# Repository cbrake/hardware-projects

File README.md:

# Hardware Projects

Various hardware projects and notes.

Simple IoT hardware designs have moved to:
https://github.com/simpleiot/hardware

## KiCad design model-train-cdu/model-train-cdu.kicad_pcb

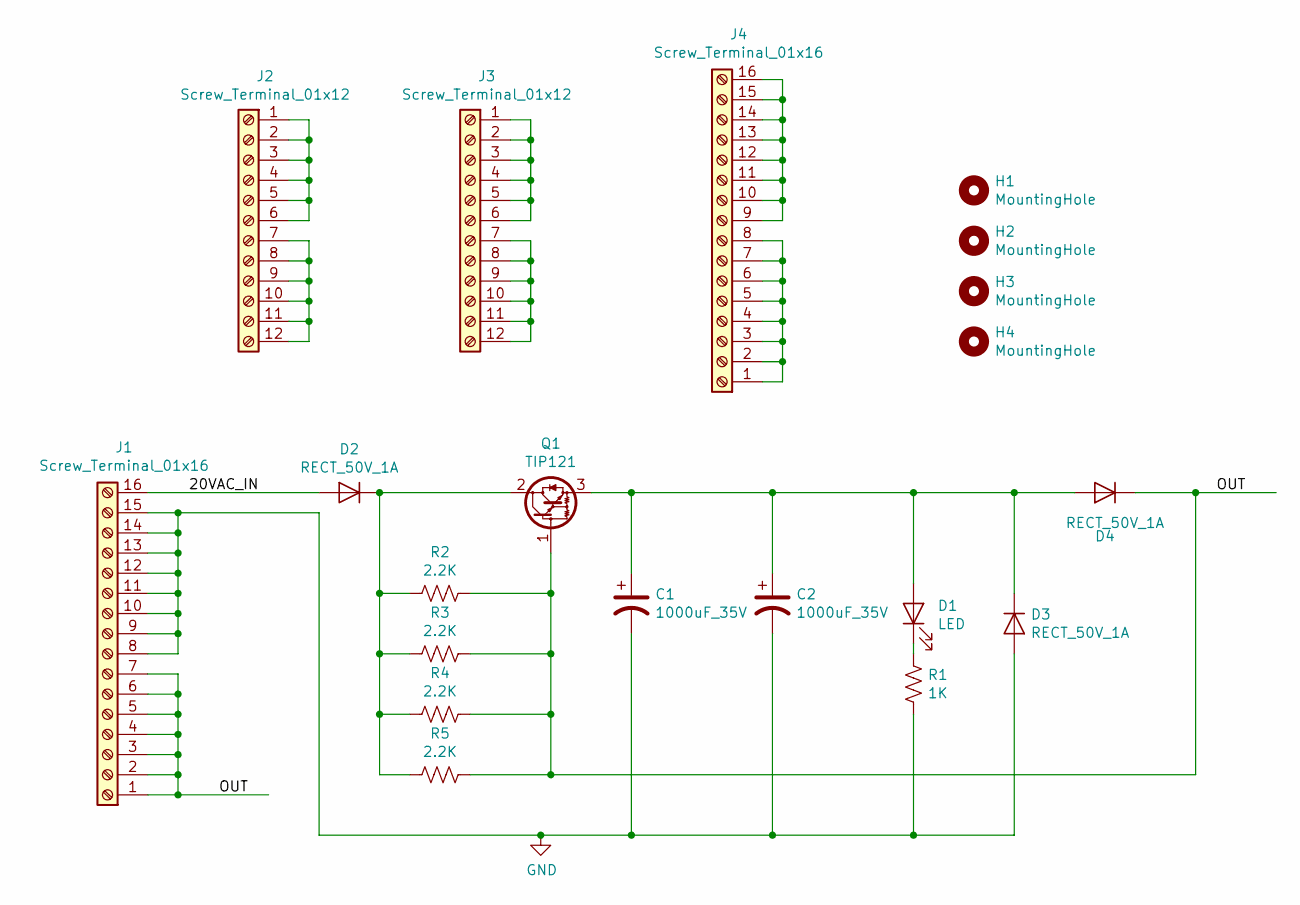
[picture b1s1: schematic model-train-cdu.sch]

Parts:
C1, C2: 1000uF_35V; CP_Radial_D10.0mm_P5.00mm; MPN EEU-FS1V102LB
D1: LED; LED_3mm_Radial
D2, D3, D4: RECT_50V_1A; D_SMA; MPN US1M-13-F
H1, H2, H3, H4: MountingHole; MountingHole_4.3mm_M4
J1, J4: Screw_Terminal_01x16; TerminalBlock_Phoenix_PT-1,5-16-5.0-H_1x16_P5.00mm_Horizont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
J2, J3: Screw_Terminal_01x12; TerminalBlock_Phoenix_PT-1,5-12-5.0-H_1x12_P5.00mm_Horizont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
Q1: TIP121; TO-220-3_Horizontal_TabDown
R1: 1K; R_1206_3216Metric
R2, R3, R4, R5: 2.2K; R_1206_3216Metric

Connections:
/20VAC_IN: D2.2 (A), J1.16
/OUT: D4.1 (K), J1.1, J1.2, J1.3, J1.4, J1.5, J1.6, J1.7, Q1.1 (B), R2.1, R3.1, R4.1, R5.1
GND: C1.2, C2.2, D3.2 (A), J1.8, J1.9, J1.10, J1.11, J1.12, J1.13, J1.14, J1.15, R1.2
unnamed: C1.1, C2.1, D1.2 (A), D3.1 (K), D4.2 (A), Q1.3 (E)
unnamed: D1.1 (K), R1.1
unnamed: D2.1 (K), Q1.2 (C), R2.2, R3.2, R4.2, R5.2
unnamed: J2.1, J2.2, J2.3, J2.4, J2.5, J2.6
unnamed: J2.7, J2.8, J2.9, J2.10, J2.11, J2.12
unnamed: J3.1, J3.2, J3.3, J3.4, J3.5, J3.6
unnamed: J3.7, J3.8, J3.9, J3.10, J3.11, J3.12
unnamed: J4.1, J4.2, J4.3, J4.4, J4.5, J4.6, J4.7, J4.8
unnamed: J4.9, J4.10, J4.11, J4.12, J4.13, J4.14, J4.15, J4.16

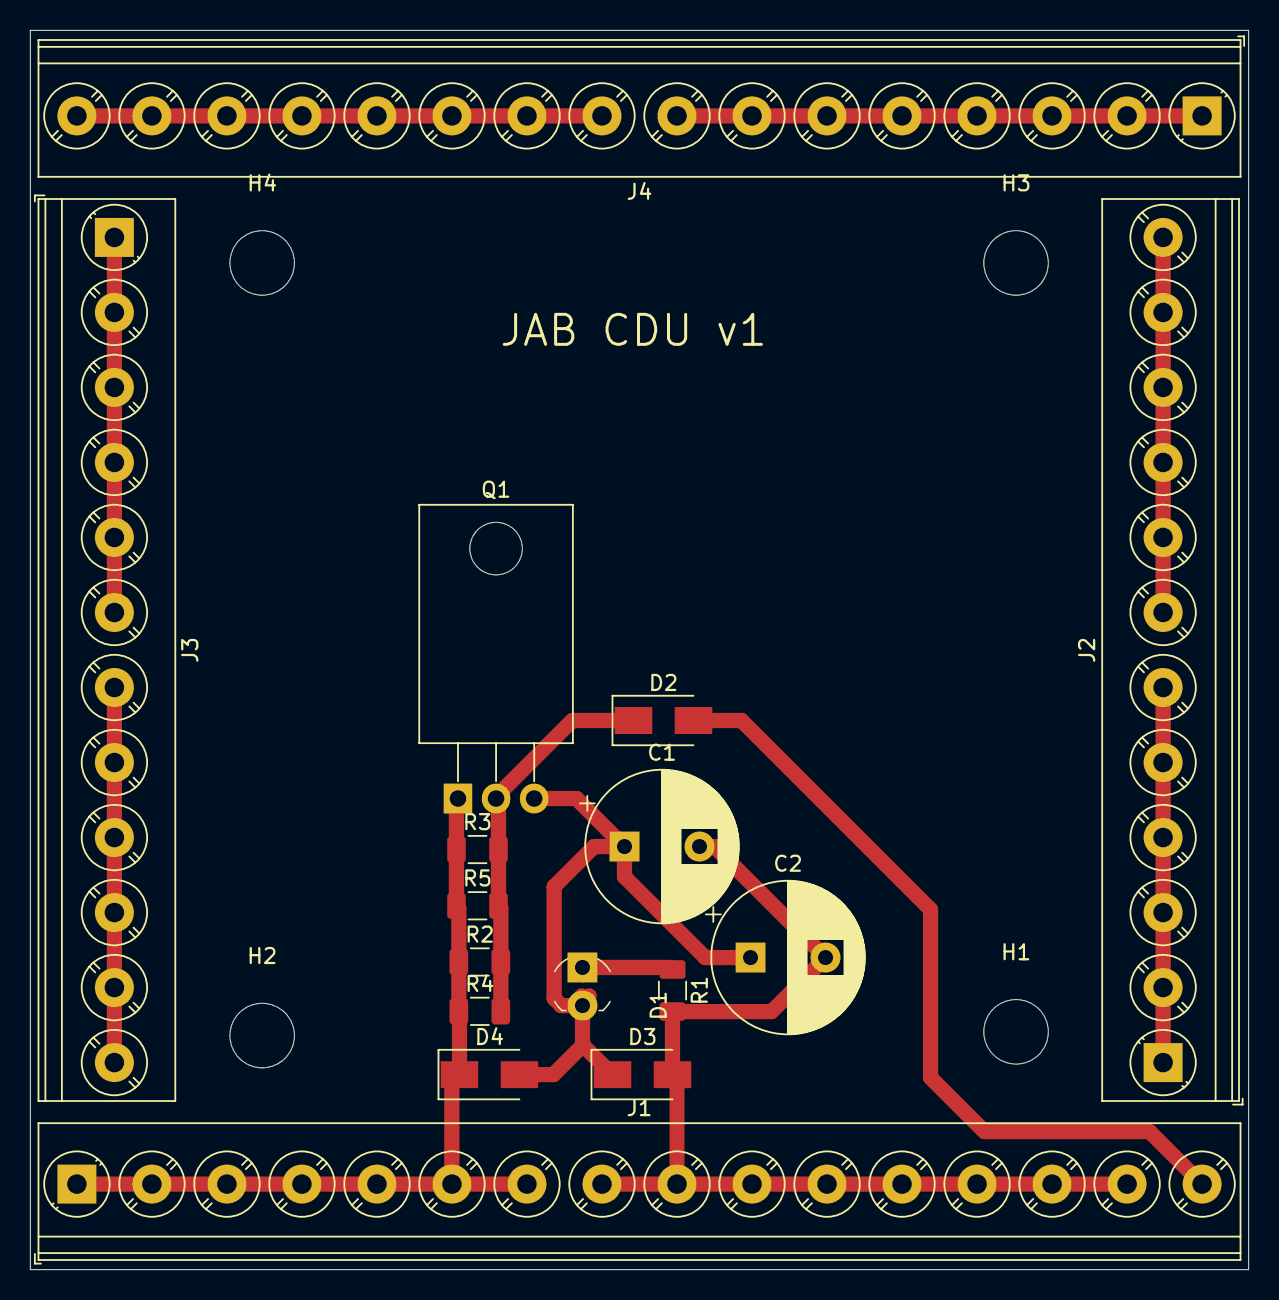
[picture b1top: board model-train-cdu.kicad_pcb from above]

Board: 2 copper layers, 81.2 x 82.6 mm, 20 parts (0 on the bottom side), 12 nets.

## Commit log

2019-09-21 remove siot stuff -- moved to https://github.com/simpleiot/hardware
2019-09-21 note on siot stuff moving
2020-01-07 add plugin to format BOM for SEEED
2020-01-07 part updates
2020-01-07 design for model train CDU
2020-03-03 add documentation
2020-03-03 add mfg files
2020-03-03 add PDF
2020-10-27 cat feeder timer using timers.shop wifi timer
2020-10-27 add more comments
2023-01-21 add 817 opto module schematics
2023-01-23 update 817 schematic
